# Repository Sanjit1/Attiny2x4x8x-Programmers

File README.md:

# Programmer for the ATTiny2/4/8 series.
These are the KiCad Files for programmers that use Arduino as ISP to program ATTinies. There is an Arduino Uno and an Arduino Nano version. There are headers for both the '5s and the '4s.

## TOC
- [TOC](#toc)
- [Convinient Links](#convinient-links)
- [Usage Guide](#usage-guide)
	- [Configuring the Arduino for In-System Programming:](#configuring-the-arduino-for-in-system-programming)
	- [Installing the AttinyCore:](#installing-the-attinycore)
	- [Programming the ATTiny:](#programming-the-attiny)
	- [Blink](#blink)
	- [Common Debugging Tips/FAQ:](#common-debugging-tipsfaq)
- [Parts Required](#parts-required)
- [The LED?](#the-led)
- [Pics or it didn't happen](#pics-or-it-didnt-happen)

## Convinient Links
 - [How to program an Attiny85](https://www.instructables.com/How-to-Program-an-Attiny85-From-an-Arduino-Uno/): This is mostly covered in this Readme tho.
 - [ATTiny 25/45/85 Pinout/Datasheet](https://ww1.microchip.com/downloads/en/devicedoc/atmel-2586-avr-8-bit-microcontroller-attiny25-attiny45-attiny85_datasheet.pdf)
 - [ATTiny 24/44/84 Pinout/Datasheet](https://ww1.microchip.com/downloads/en/DeviceDoc/doc8006.pdf)

## Usage Guide
This should be fairly simple to setup. You can read a general guide over [here](https://www.instructables.com/How-to-Program-an-Attiny85-From-an-Arduino-Uno/). All this PCB does is replace the wiring to make life easier.
I will be doing this in Arduino Legacy using [Damellis'](https://github.com/damellis/attiny) core. If you want to use 2.0 or [SpenceKonde's](https://github.com/SpenceKonde/ATTinyCore) core, you can do that too. Just make sure to configure it properly.

### Configuring the Arduino for In-System Programming:
You only need to do this once. If the programmer has already been set up you don't need to do this again.
 1. Open the ArduinoISP sketch from File > Examples > ArduinoISP.
 2. Correctly select the Arduino Uno/Nano as your board and the correct port.
 3. Make sure that the reset capacitor switch is facing the cap, otherwise it will mess with the programming.
 4. Upload!

### Installing the AttinyCore:
 1. Go to Arduino IDE > File > Preferences > Additional Boards Manager URLs.
 2. Add `https://raw.githubusercontent.com/damellis/attiny/ide-1.6.x-boards-manager/package_damellis_attiny_index.json` to the list.
 3. Open the Boards Manager from Tools > Board > Boards Manager.
 4. Search for `ATTinyCore` and install it.

### Programming the ATTiny:
 1. You will have to edit a bunch of options in `Tools`: Board, Processor, Clock, Port and Programmer.
 2. Board and Processor: Correctly select what ATTiny you are using(25/45/85/24/44/84)
 3. Clock: Unless you know what you are doing, select one of the Internal clocks.
 4. Port: Select the port that the Arduino is connected to.
 5. Programmer: Select `Arduino as ISP`.
 6. If this is the first time you are using that ATTiny, you may need to burn the bootloader. This is done by selecting `Burn Bootloader`.
 7. Use keyboard shortcut `Ctrl+Shift+U` to `Upload Using Programmer`.

Keep in mind that if you want to program and arduino after this ,you will need to change the programmer back to `AVRISP mkII` or whatever you were using.

### Blink
I have provided a sample blink sketch. If you find that the LED is blinking faster/slower than expected, you may need to change the clock speed. This is done by burning the bootloader again.

### Common Debugging Tips/FAQ:
 - If Arduino IDE cant find the Arduino Nano or you cant see a change in the port list, install the [CH340](https://learn.sparkfun.com/tutorials/how-to-install-ch340-drivers/all) driver.
 - If you can't upload the sketch, make sure that the programmer is set to `Arduino as ISP`.
 - If you are getting `avrdude: stk500_getsync() attempt 10 of 10: not in sync: resp=0x00`, this is usually a wiring issue or incorrect programmer selected.
 - If you are getting `avrdude: Yikes!  Invalid device signature.`, this is usually a wiring issue or incorrect ATTiny selected.

## Parts Required
 - 1x Arduino Nano/Uno
 - 1x Arduino Nano Header/Male Headers for the Uno
 - 2x 15-pin headers if you are using the Nano version(Optional)
 - 2x 7-pin headers + 2x 4-pin headers if you are using the Uno version(Optional)
 - 1x 10uF capacitor(elecrolytic/ceramic is fine)
 - 1x 14-pin DIP socket
 - 1x 8-pin DIP socket
 - 1x Switch
 - 1x 2x3 ICSP header(optional)
 - 1x LED (optional)
 - 1x 220 Ohm resistor (optional)

## The LED?
Yea, there is an LED connected to MISO. With that, you can have a startup script that helps you verify that your program successfully uploaded.

On an Attiny85: MISO is Pin 6(**PB1**)

On an Attiny84: MISO is Pin 8(**PB5**)

## Pics or it didn't happen

I will take an IRL pic later.

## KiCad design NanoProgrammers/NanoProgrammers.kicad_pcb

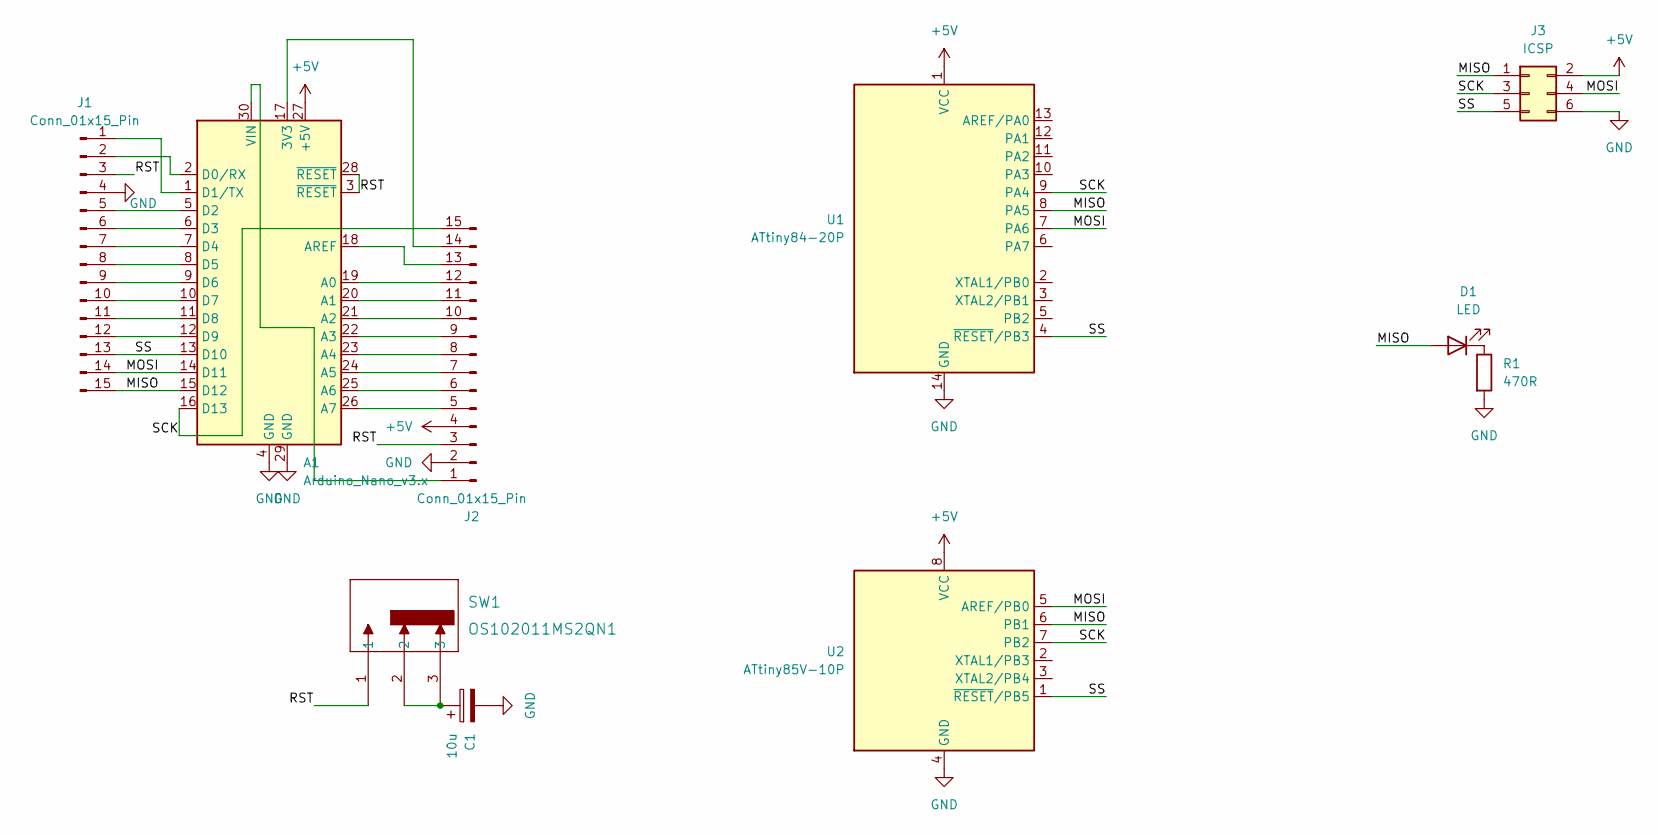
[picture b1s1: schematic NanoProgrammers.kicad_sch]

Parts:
A1: Arduino_Nano_v3.x; Arduino_Nano
C1: 10u; CP_Radial_D5.0mm_P2.50mm
D1: LED; LED_D4.0mm
J1, J2: Conn_01x15_Pin; PinHeader_1x15_P2.54mm_Vertical
J3: ICSP; PinHeader_2x03_P2.54mm_Vertical
R1: 470R; R_Axial_DIN0207_L6.3mm_D2.5mm_P10.16mm_Horizontal
SW1: OS102011MS2QN1; SPDT_OS102011_CNK
U1: ATtiny84-20P; DIP-14_W7.62mm
U2: ATtiny85V-10P; DIP-8_W7.62mm

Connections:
+5V: A1.27 (+5V), J2.4, J3.2, U1.1 (VCC), U2.8 (VCC)
/MISO: A1.15 (D12), D1.2 (A), J1.15, J3.1, U1.8 (PA5), U2.6 (PB1)
/MOSI: A1.14 (D11), J1.14, J3.4, U1.7 (PA6), U2.5 (AREF/PB0)
/RST: A1.3 (~RESET), A1.28 (~RESET), J1.3, J2.3, SW1.1
/SCK: A1.16 (D13), J2.15, J3.3, U1.9 (PA4), U2.7 (PB2)
/SS: A1.13 (D10), J1.13, J3.5, U1.4 (~RESET/PB3), U2.1 (~RESET/PB5)
GND: A1.4 (GND), A1.29 (GND), C1.2, J1.4, J2.2, J3.6, R1.2, U1.14 (GND), U2.4 (GND)
unnamed: A1.17 (3V3), J2.14
unnamed: A1.19 (A0), J2.12
unnamed: A1.20 (A1), J2.11
unnamed: A1.21 (A2), J2.10
unnamed: A1.22 (A3), J2.9
unnamed: A1.23 (A4), J2.8
unnamed: A1.24 (A5), J2.7
unnamed: A1.25 (A6), J2.6
unnamed: A1.26 (A7), J2.5
unnamed: A1.18 (AREF), J2.13
unnamed: A1.2 (D0/RX), J1.2
unnamed: A1.1 (D1/TX), J1.1
unnamed: A1.5 (D2), J1.5
unnamed: A1.6 (D3), J1.6
unnamed: A1.7 (D4), J1.7
unnamed: A1.8 (D5), J1.8
unnamed: A1.9 (D6), J1.9
unnamed: A1.10 (D7), J1.10
unnamed: A1.11 (D8), J1.11
unnamed: A1.12 (D9), J1.12
unnamed: A1.30 (VIN), J2.1
unnamed: C1.1, SW1.2, SW1.3
unnamed: D1.1 (K), R1.1

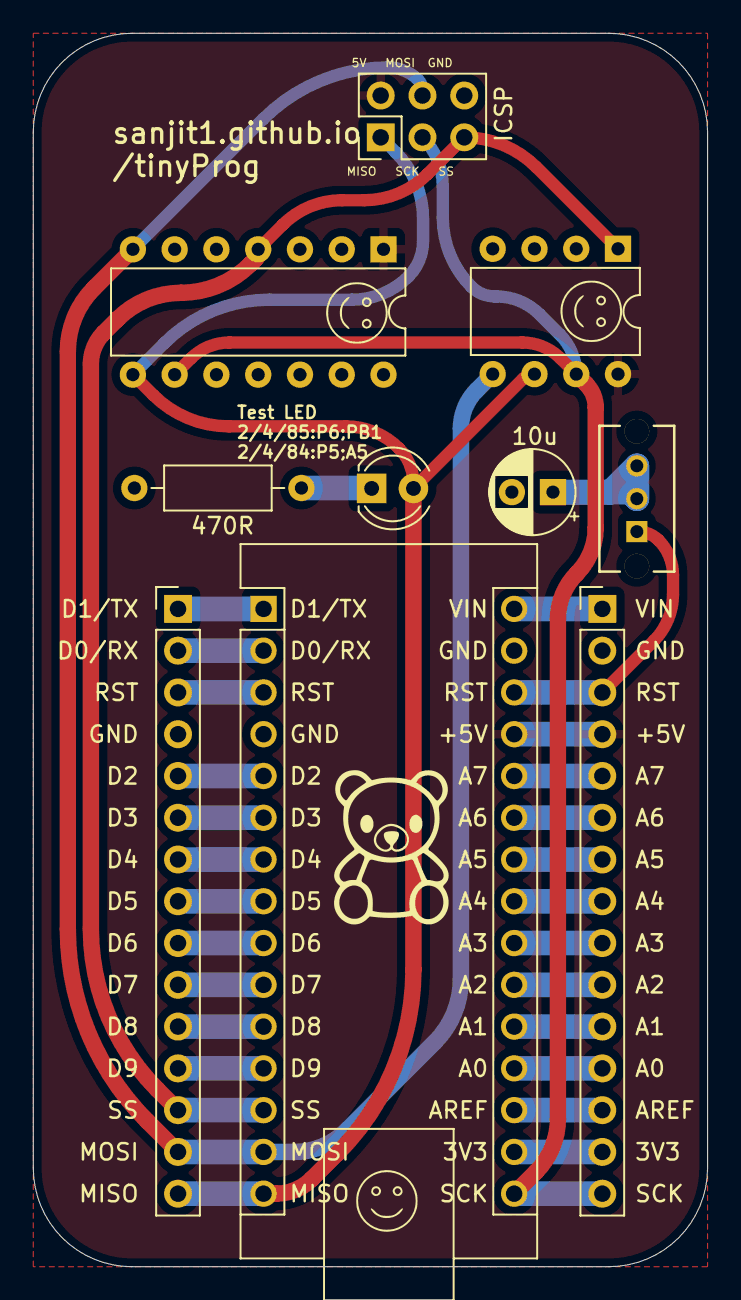
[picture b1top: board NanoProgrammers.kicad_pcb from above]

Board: 2 copper layers, 41.0 x 75.0 mm, 13 parts (0 on the bottom side), 30 nets.

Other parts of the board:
G1, G2, G3: LOGO; Smiley Face

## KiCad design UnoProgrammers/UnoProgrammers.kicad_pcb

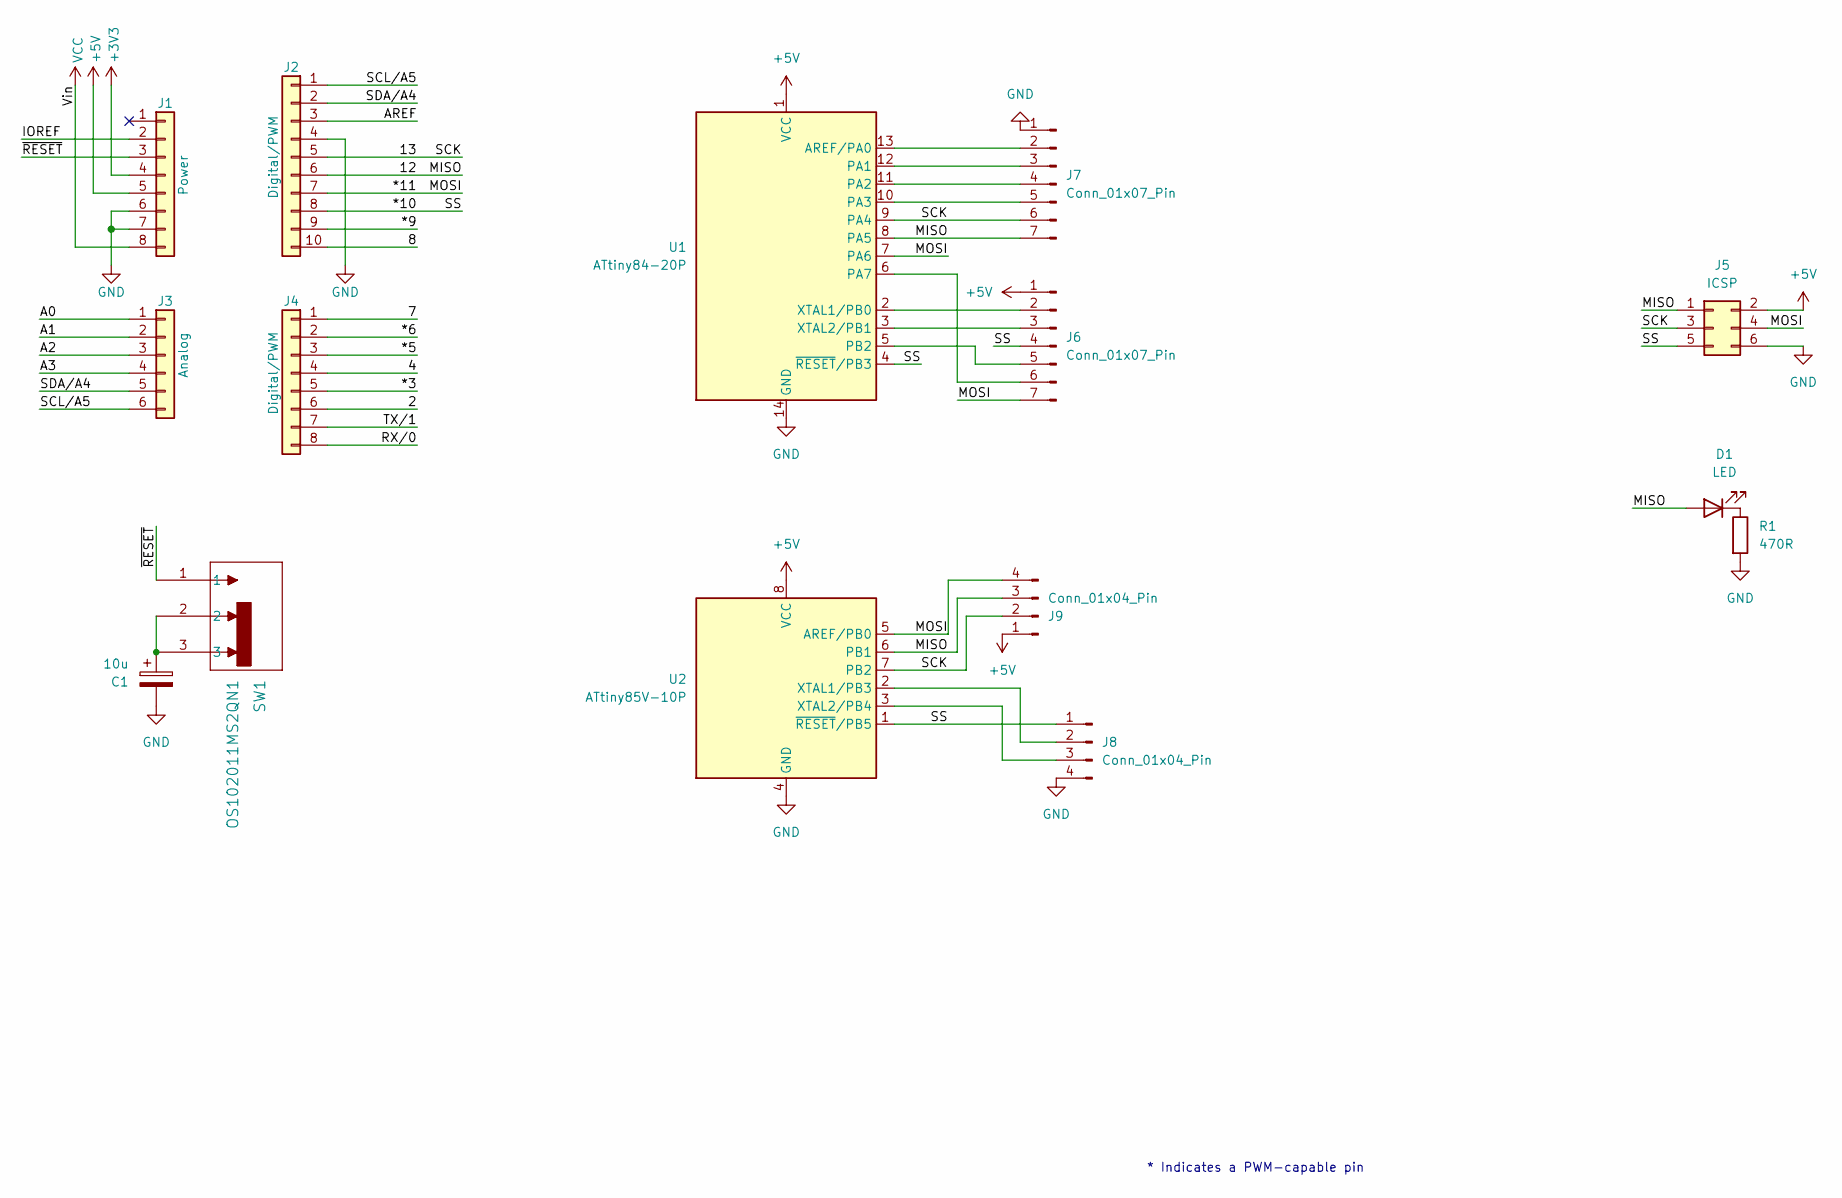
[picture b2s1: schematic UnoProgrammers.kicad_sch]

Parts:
C1: 10u; CP_Radial_D5.0mm_P2.50mm
D1: LED; LED_D4.0mm
J1: Power; PinSocket_1x08_P2.54mm_Vertical
J2: Digital/PWM; PinSocket_1x10_P2.54mm_Vertical
J3: Analog; PinSocket_1x06_P2.54mm_Vertical
J4: Digital/PWM; PinSocket_1x08_P2.54mm_Vertical
J5: ICSP; PinHeader_2x03_P2.54mm_Vertical
J6, J7: Conn_01x07_Pin; PinHeader_1x07_P2.54mm_Vertical
J8, J9: Conn_01x04_Pin; PinHeader_1x04_P2.54mm_Vertical
R1: 470R; R_Axial_DIN0207_L6.3mm_D2.5mm_P10.16mm_Horizontal
SW1: OS102011MS2QN1; SPDT_OS102011_CNK
U1: ATtiny84-20P; DIP-14_W7.62mm
U2: ATtiny85V-10P; DIP-8_W7.62mm

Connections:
+3V3: J1.4
+5V: J1.5, J5.2, J6.1, J9.1, U1.1 (VCC), U2.8 (VCC)
/2: J4.6
/4: J4.4
/7: J4.1
/8: J2.10
/12: D1.2 (A), J2.6, J5.1, J7.7, J9.3, U1.8 (PA5), U2.6 (PB1)
/13: J2.5, J5.3, J7.6, J9.2, U1.9 (PA4), U2.7 (PB2)
/*3: J4.5
/*5: J4.3
/*6: J4.2
/*9: J2.9
/*10: J2.8, J5.5, J6.4, J8.1, U1.4 (~RESET/PB3), U2.1 (~RESET/PB5)
/*11: J2.7, J5.4, J6.7, J9.4, U1.7 (PA6), U2.5 (AREF/PB0)
/A0: J3.1
/A1: J3.2
/A2: J3.3
/A3: J3.4
/AREF: J2.3
/IOREF: J1.2
/RX/0: J4.8
/SCL/A5: J2.1, J3.6
/SDA/A4: J2.2, J3.5
/TX/1: J4.7
/~RESET: J1.3, SW1.1
GND: C1.2, J1.6, J1.7, J2.4, J5.6, J7.1, J8.4, R1.2, U1.14 (GND), U2.4 (GND)
unnamed: C1.1, SW1.2, SW1.3
unnamed: D1.1 (K), R1.1
unnamed: J6.2, U1.2 (XTAL1/PB0)
unnamed: J6.3, U1.3 (XTAL2/PB1)
unnamed: J6.5, U1.5 (PB2)
unnamed: J6.6, U1.6 (PA7)
unnamed: J7.2, U1.13 (AREF/PA0)
unnamed: J7.3, U1.12 (PA1)
unnamed: J7.4, U1.11 (PA2)
unnamed: J7.5, U1.10 (PA3)
unnamed: J8.2, U2.2 (XTAL1/PB3)
unnamed: J8.3, U2.3 (XTAL2/PB4)
VCC: J1.8

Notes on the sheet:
* Indicates a PWM-capable pin

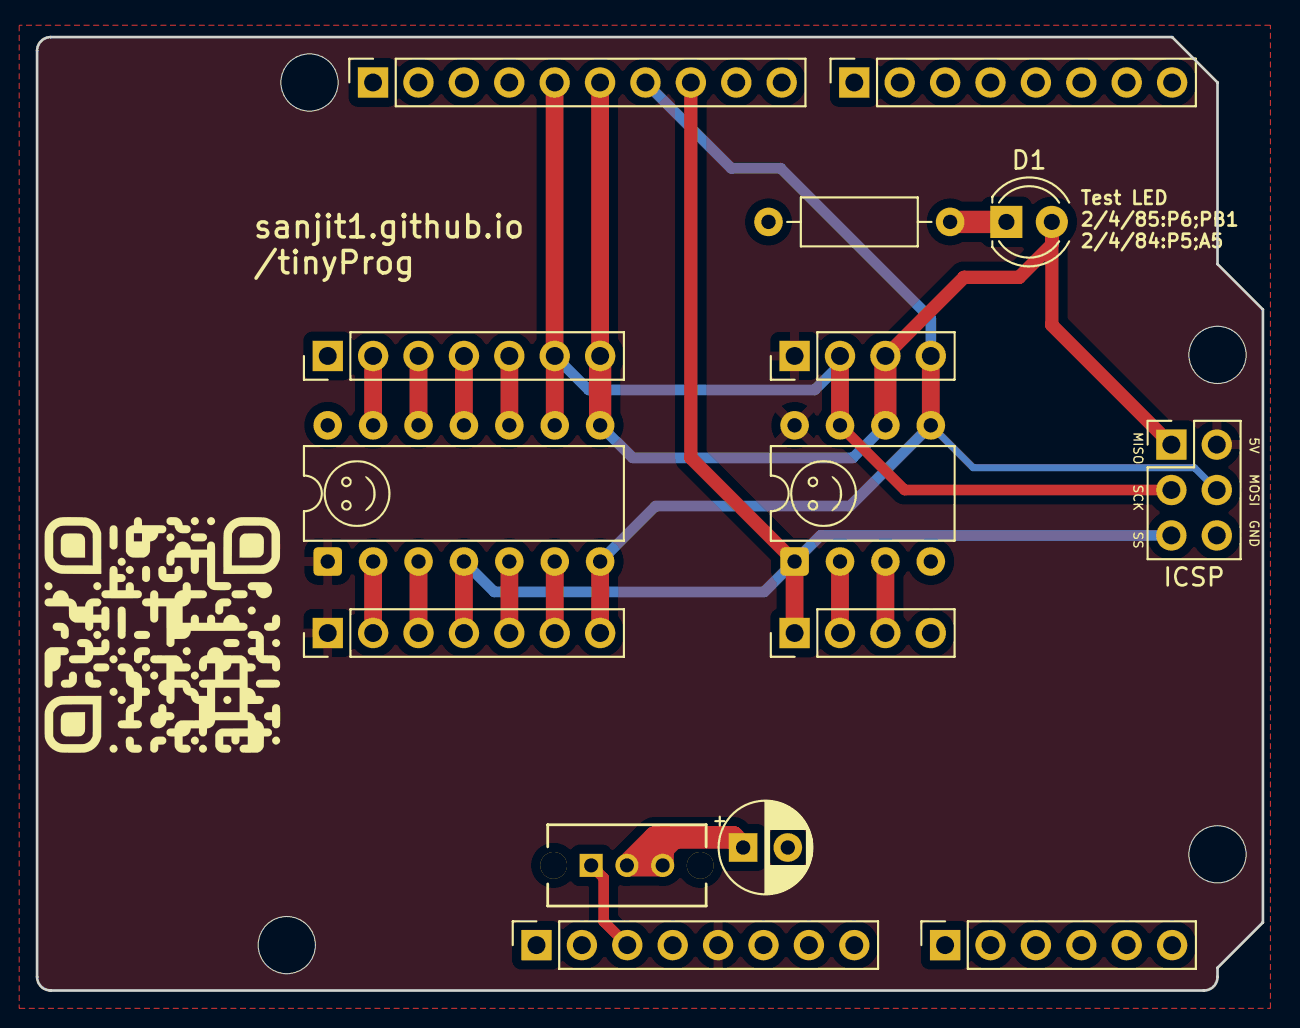
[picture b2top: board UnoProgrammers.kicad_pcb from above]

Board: 2 copper layers, 68.6 x 53.3 mm, 21 parts (0 on the bottom side), 21 nets.

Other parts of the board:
G2, G2#2: LOGO; Smiley Face
MH1, MH2, MH3, MH4: MountingHole_3.2mm

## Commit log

2025-01-26 readme
2025-02-12 Not sure why I backed that up
2025-02-22 Formatting
2025-03-04 Split into Nano and Uno programmer
2025-03-04 Some Readme updates
